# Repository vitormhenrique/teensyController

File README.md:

Teensy based controller.

TODO: description, bill of materials and etc

The entire project is under GPL-3.0, that means basically that you can use, copy, modify and basically do whatever you want with it.

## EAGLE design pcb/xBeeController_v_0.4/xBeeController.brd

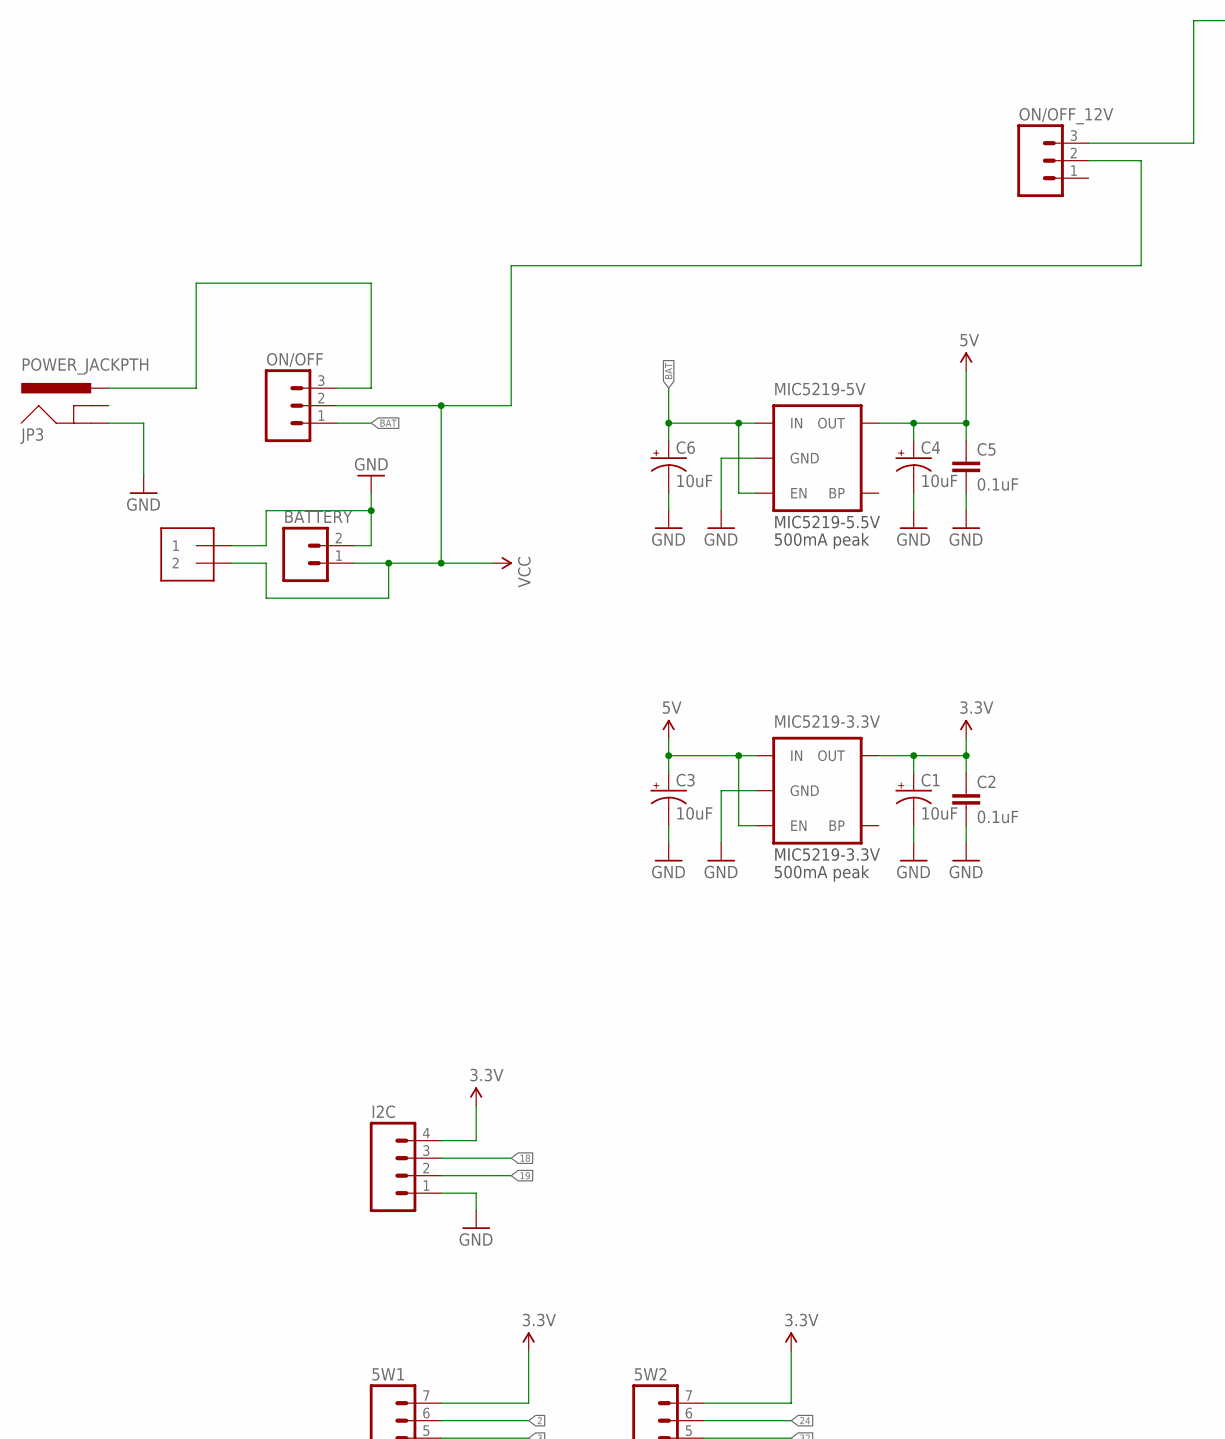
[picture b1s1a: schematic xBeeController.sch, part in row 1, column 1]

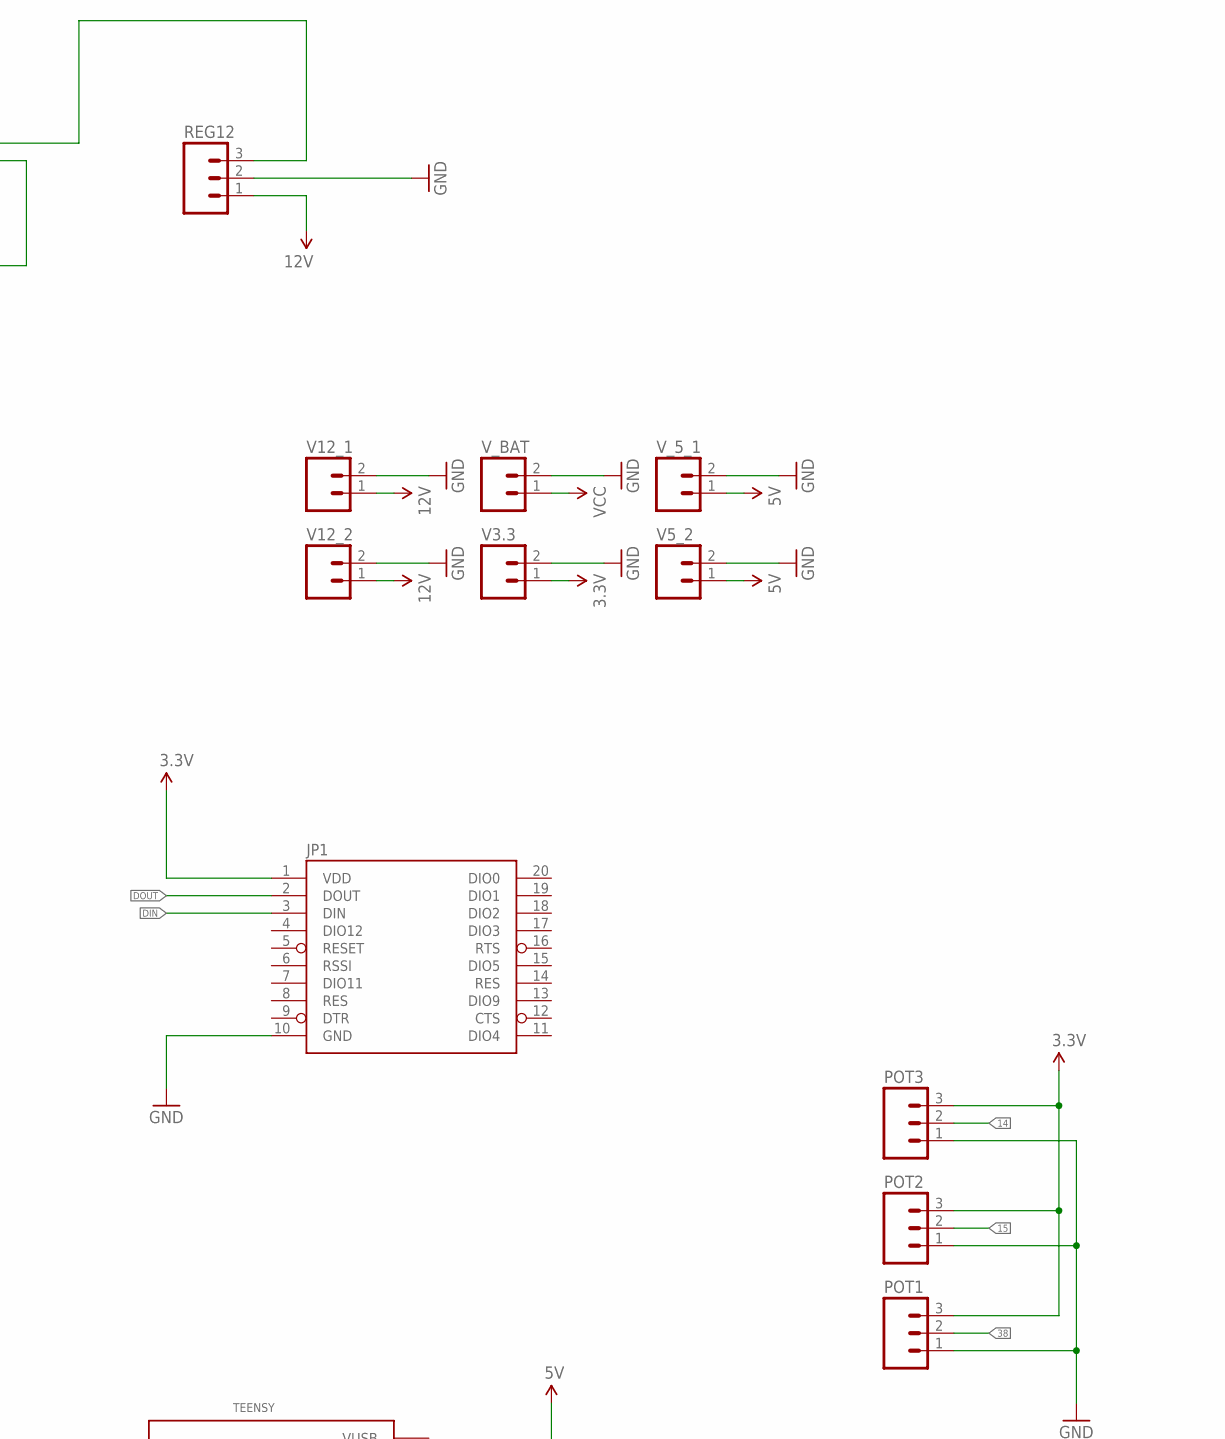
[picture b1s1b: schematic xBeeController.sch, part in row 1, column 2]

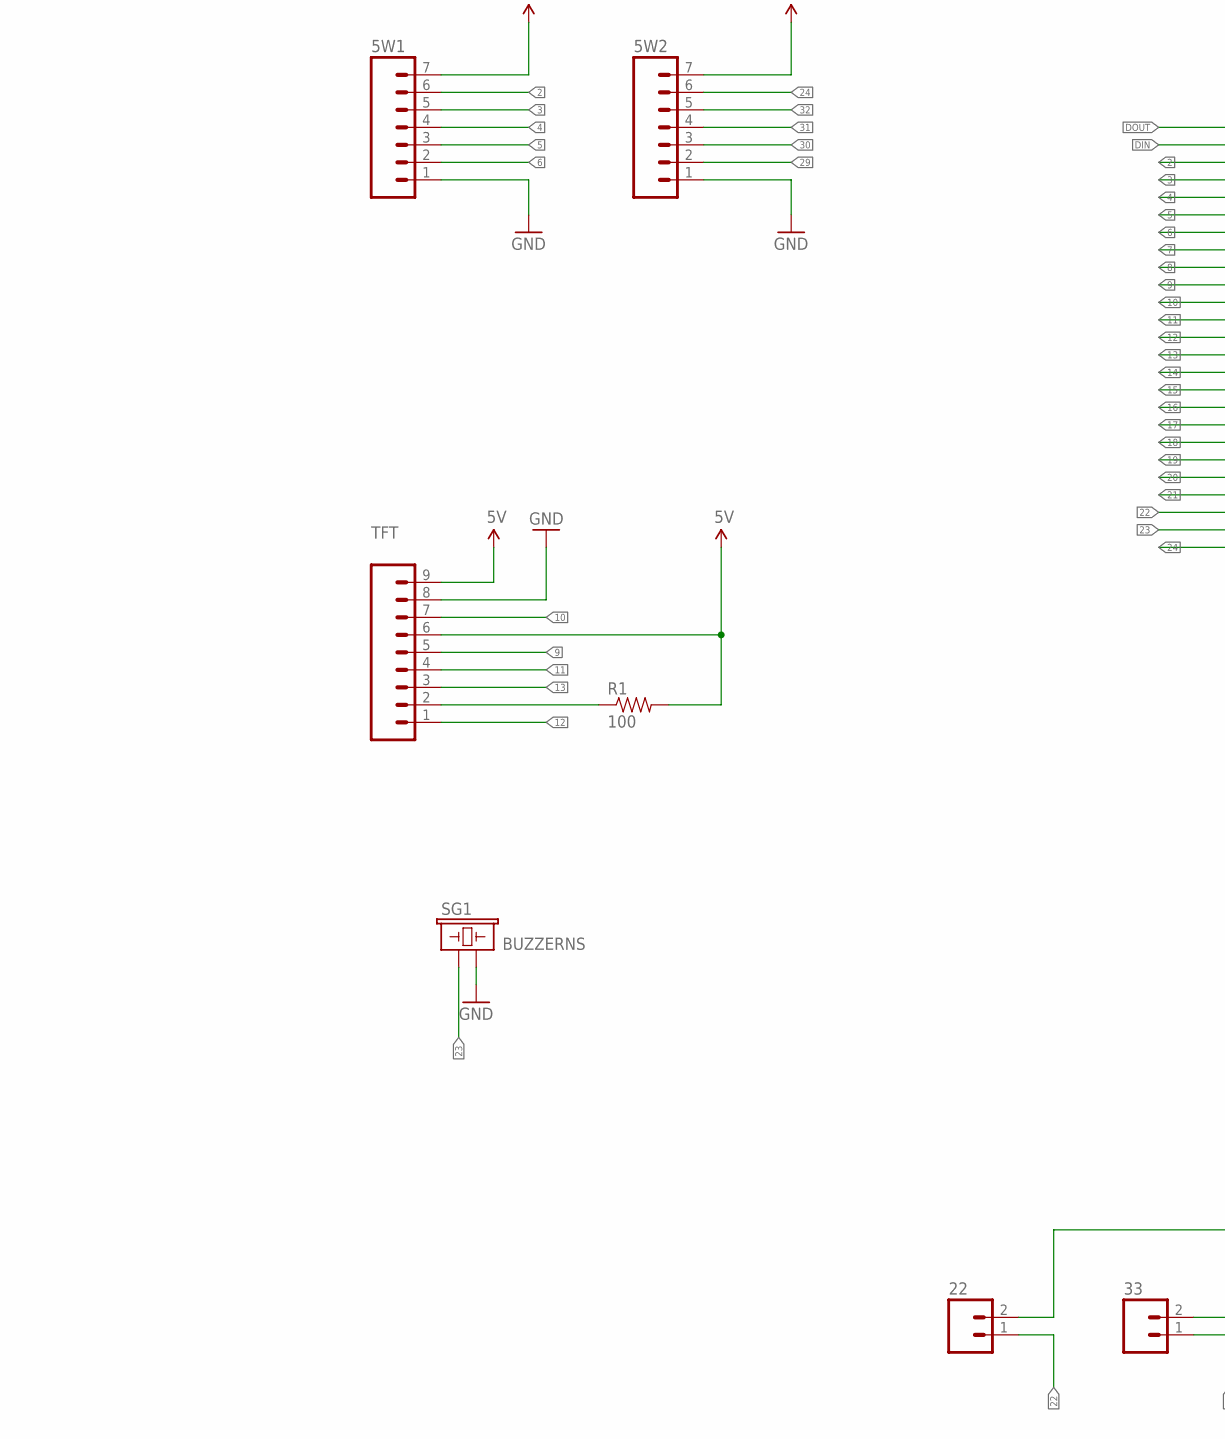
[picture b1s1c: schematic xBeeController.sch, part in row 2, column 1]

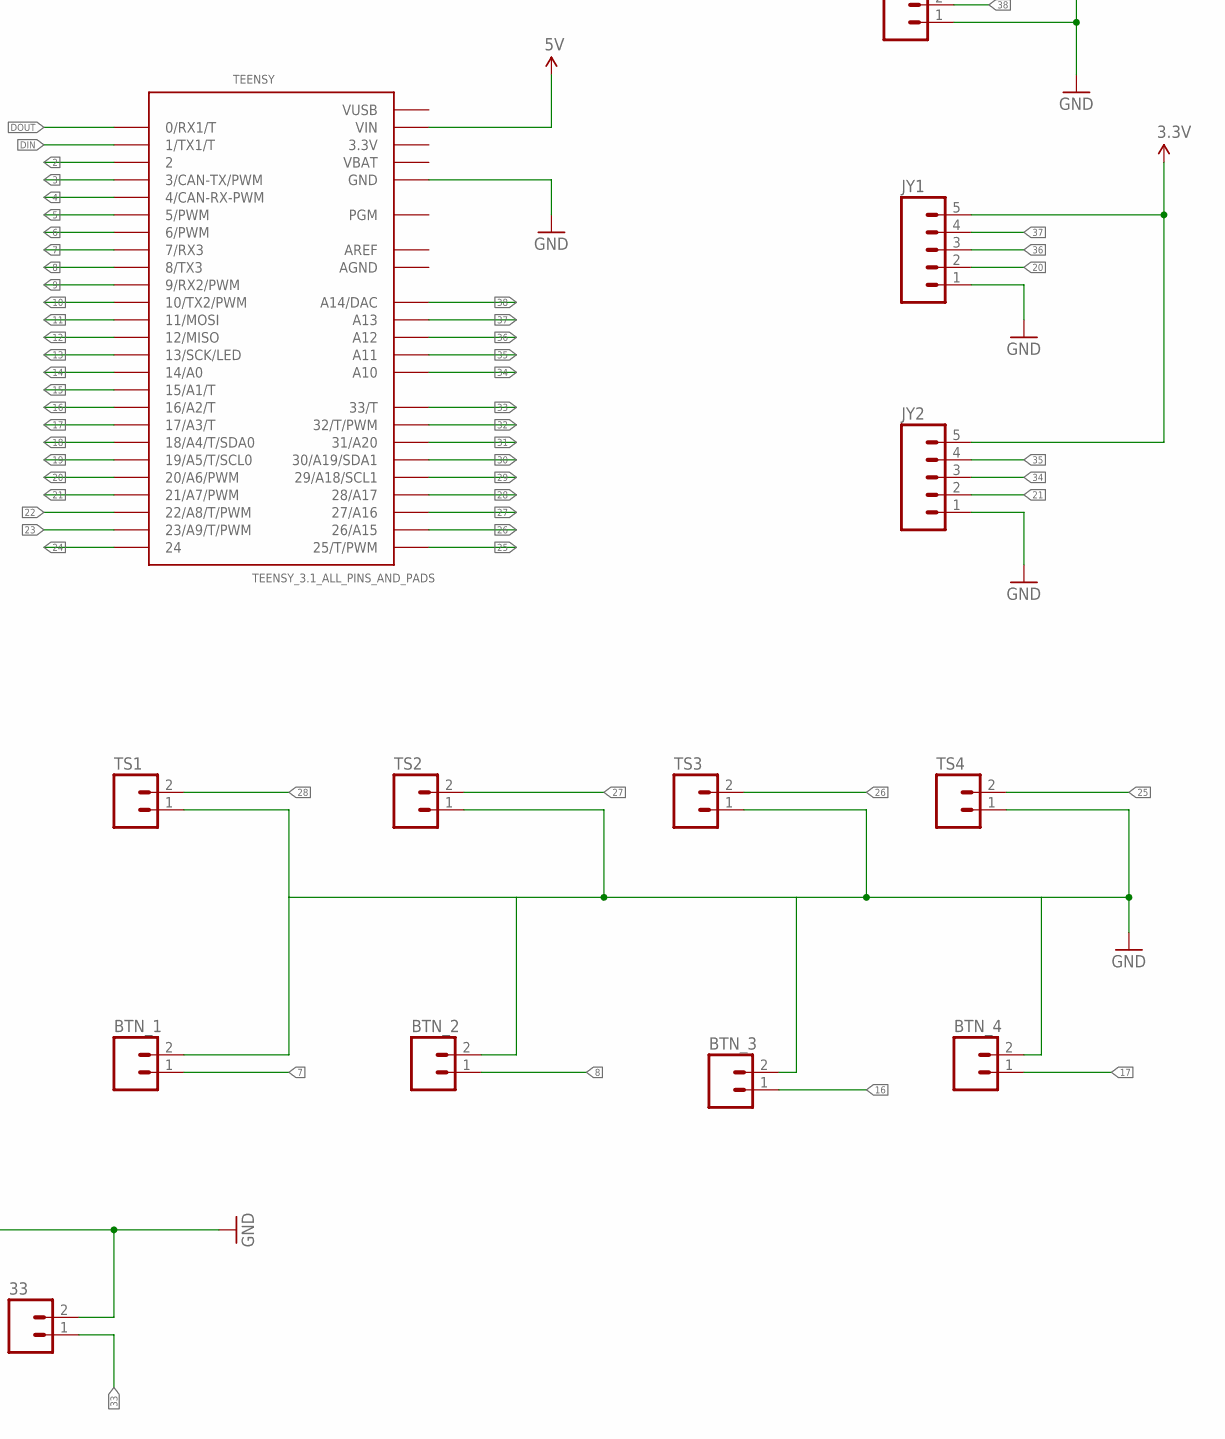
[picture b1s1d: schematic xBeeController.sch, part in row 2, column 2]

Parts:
5W1, 5W2: M07; 1X07
22, 33: M02PTH; 1X02
BATTERY: M02PTH; 1X02
BTN_1, BTN_2, BTN_3, BTN_4: M02PTH; 1X02
C1, C3, C4, C6: 10uF; EIA3528
C2, C5: 0.1uF; 0805
I2C: M04PTH; 1X04
J1: TERMBLOCK_1X2-3.5MM; 1X2-3.5MM
JP1: XBEE-1B1; XBEE-1
JP3: POWER_JACKPTH; POWER_JACK_PTH
JY1, JY2: M05PTH; 1X05
MIC5219-3.3V, MIC5219-5V: V_REG_LDOSMD; SOT23-5
ON/OFF: M03PTH; 1X03
ON/OFF_12V: M03PTH; 1X03
POT1, POT2, POT3: M03PTH; 1X03
R1: 100; 0805
REG12: M03PTH; 1X03
SG1: BUZZERNS; BUZZER-12MM-NS
TEENSY: TEENSY_3.1_ALL_PINS_AND_PADS; TEENSY_3.1_ALLPINS
TFT: M09; 1X09
TS1, TS2, TS3, TS4: M02PTH; 1X02
V3.3, V5_2, V12_1, V12_2: M02PTH; 1X02
V_5_1: M02PTH; 1X02
V_BAT: M02PTH; 1X02

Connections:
2: 5W1.6, TEENSY.2
3: 5W1.5, TEENSY.3 (3/CAN-TX/PWM)
3.3V: 5W1.7, 5W2.7, C1.A (+), C2.1, I2C.4, JP1.1 (VDD), JY1.5, JY2.5, MIC5219-3.3V.5 (OUT), POT1.3, POT2.3, POT3.3, TEENSY.3.3V, TEENSY.3.3V1 (3.3V), TEENSY.3.3V2 (3.3V), V3.3.1
4: 5W1.4, TEENSY.4 (4/CAN-RX-PWM)
5: 5W1.3, TEENSY.5 (5/PWM)
5V: C3.A (+), C4.A (+), C5.1, MIC5219-3.3V.1 (IN), MIC5219-3.3V.3 (EN), MIC5219-5V.5 (OUT), R1.2, TEENSY.VIN, TFT.6, TFT.9, V5_2.1, V_5_1.1
6: 5W1.2, TEENSY.6 (6/PWM)
7: BTN_1.1, TEENSY.7 (7/RX3)
8: BTN_2.1, TEENSY.8 (8/TX3)
9: TEENSY.9 (9/RX2/PWM), TFT.5
10: TEENSY.10 (10/TX2/PWM), TFT.7
11: TEENSY.11 (11/MOSI), TFT.4
12: TEENSY.12 (12/MISO), TFT.1
12V: REG12.1, V12_1.1, V12_2.1
13: TEENSY.13 (13/SCK/LED), TFT.3
14: POT3.2, TEENSY.14/A0
15: POT2.2, TEENSY.15/A1 (15/A1/T)
16: BTN_3.1, TEENSY.16/A2 (16/A2/T)
17: BTN_4.1, TEENSY.17/A3 (17/A3/T)
18: I2C.3, TEENSY.18/A4 (18/A4/T/SDA0)
19: I2C.2, TEENSY.19/A5 (19/A5/T/SCL0)
20: JY1.2, TEENSY.20/A6 (20/A6/PWM)
21: JY2.2, TEENSY.21/A7 (21/A7/PWM)
22: 22.1, TEENSY.22/A8 (22/A8/T/PWM)
23: SG1.+ (1), TEENSY.23/A9 (23/A9/T/PWM)
24: 5W2.6, TEENSY.24
25: TEENSY.25 (25/T/PWM), TS4.2
26: TEENSY.26 (26/A15), TS3.2
27: TEENSY.27 (27/A16), TS2.2
28: TEENSY.28 (28/A17), TS1.2
29: 5W2.2, TEENSY.29 (29/A18/SCL1)
30: 5W2.3, TEENSY.30 (30/A19/SDA1)
31: 5W2.4, TEENSY.31 (31/A20)
32: 5W2.5, TEENSY.32 (32/T/PWM)
33: 33.1, TEENSY.33 (33/T)
34: JY2.3, TEENSY.A10
35: JY2.4, TEENSY.A11
36: JY1.3, TEENSY.A12
37: JY1.4, TEENSY.A13
38: POT1.2, TEENSY.A14 (A14/DAC)
AGND: TEENSY.AGND
AREF: TEENSY.AREF
BAT: C6.A (+), MIC5219-5V.1 (IN), MIC5219-5V.3 (EN), ON/OFF.1
DIN: JP1.3 (DIN), TEENSY.1 (1/TX1/T)
DOUT: JP1.2 (DOUT), TEENSY.0 (0/RX1/T)
GND: 5W1.1, 5W2.1, 22.2, 33.2, BATTERY.2, BTN_1.2, BTN_2.2, BTN_3.2, BTN_4.2, C1.C (-), C2.2, C3.C (-), C4.C (-), C5.2, C6.C (-), I2C.1, J1.1, JP1.10 (GND), JP3.GND, JY1.1, JY2.1, MIC5219-3.3V.2 (GND), MIC5219-5V.2 (GND), POT1.1, POT2.1, POT3.1, REG12.2, SG1.- (2), TEENSY.GND, TEENSY.GND1 (GND), TEENSY.GND2 (GND), TFT.8, TS1.1, TS2.1, TS3.1, TS4.1, V3.3.2, V5_2.2, V12_1.2, V12_2.2, V_5_1.2, V_BAT.2
unnamed: R1.1, TFT.2
unnamed: JP3.PWR, ON/OFF.3
unnamed: ON/OFF_12V.3, REG12.3
VBAT: TEENSY.VBAT
VCC: BATTERY.1, J1.2, ON/OFF.2, ON/OFF_12V.2, V_BAT.1
VUSB: TEENSY.VUSB

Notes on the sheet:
MIC5219-3.3V
500mA peak
MIC5219-5.5V

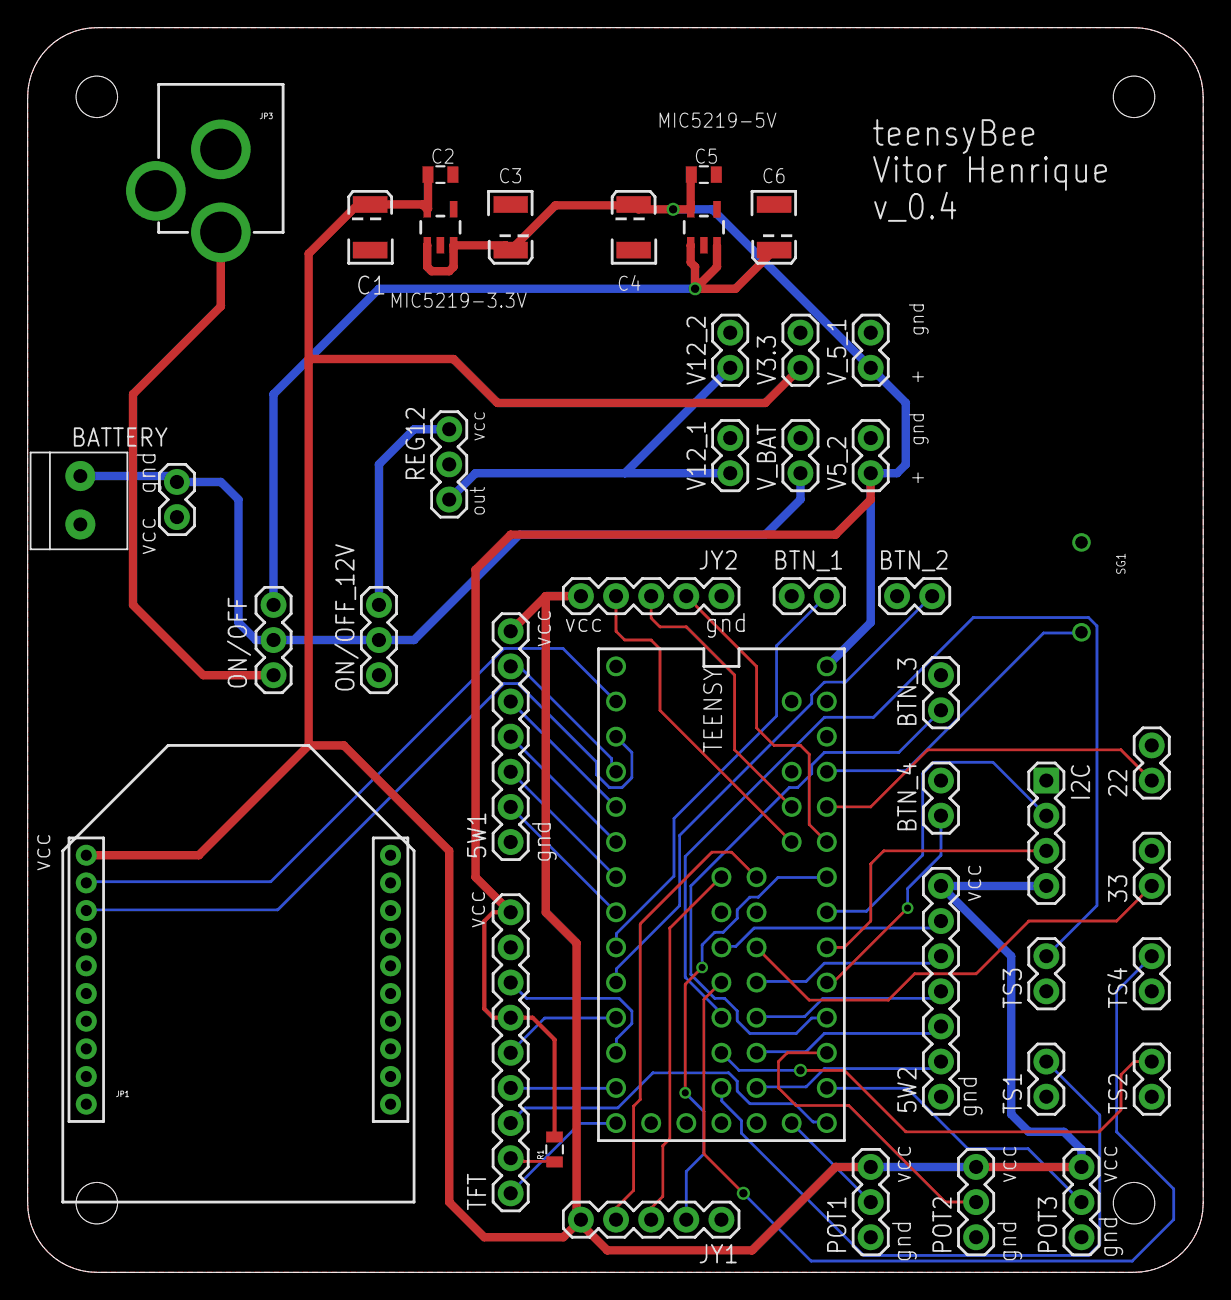
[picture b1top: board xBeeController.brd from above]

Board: 2 copper layers, 85.0 x 90.0 mm, 43 parts (0 on the bottom side), 48 nets.

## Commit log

2015-09-18 Adding stl files and correcting the freecad file for the supperior part of the remote.

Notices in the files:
parts and their libraries:
SparkFun-RF: Licensing: Creative Commons ShareAlike 4.0 International - https://creativecommons.org/licenses/by-sa/4.0
